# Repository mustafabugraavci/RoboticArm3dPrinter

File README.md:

# RoboticArm3dPrinter
Some kind of 3d printer

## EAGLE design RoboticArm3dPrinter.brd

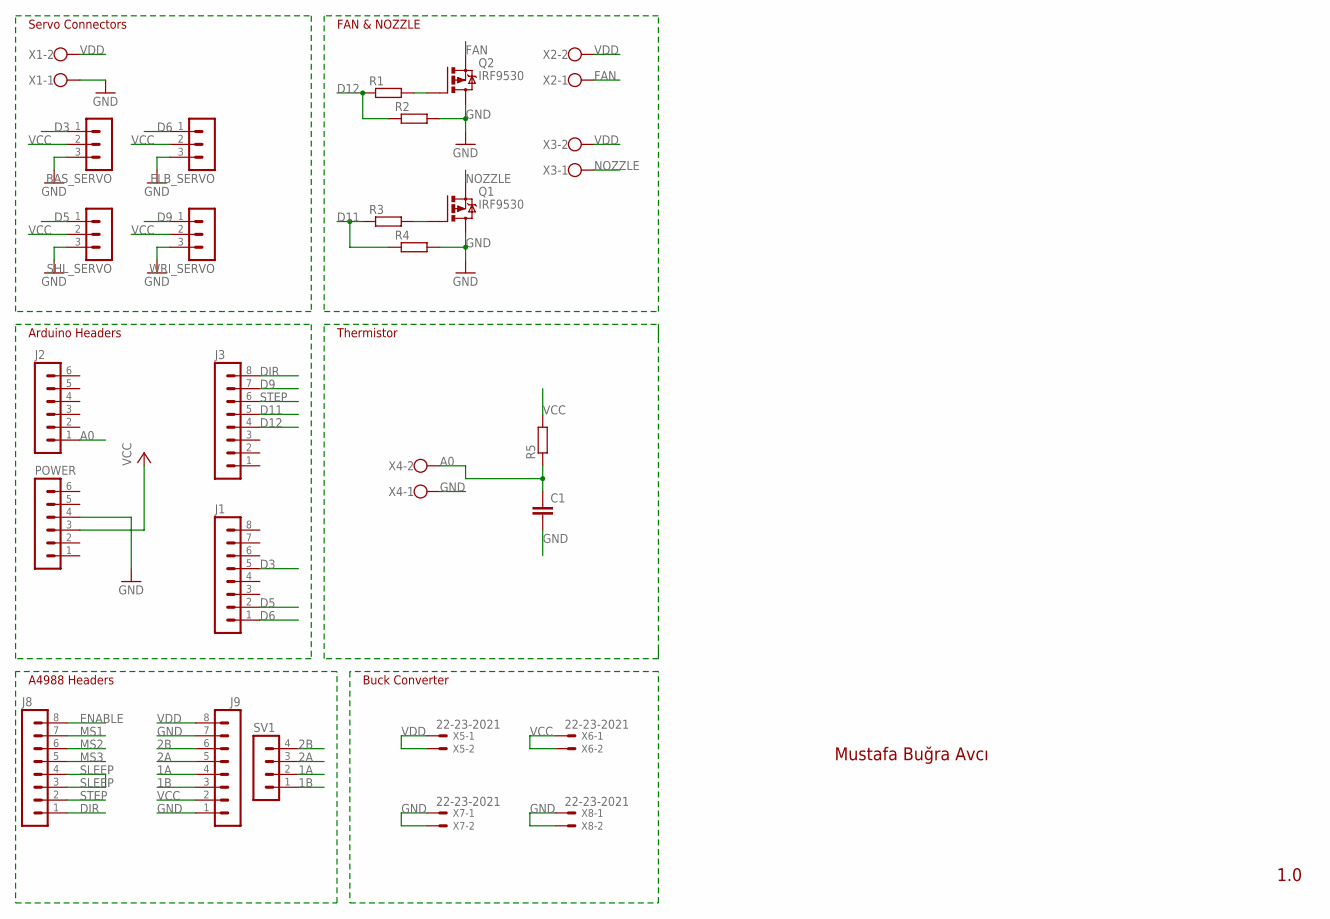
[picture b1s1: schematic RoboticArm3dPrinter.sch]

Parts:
BAS_SERVO: MA03-1
C1: C5/2.5; C5B2.5
ELB_SERVO: MA03-1
J1, J3, J8, J9: MA08-1
J2: MA06-1
POWER: MA06-1
Q1, Q2: IRF9530; TO220BV
R1, R2, R3, R4, R5: R-EU_0207/10; 0207/10
SHL_SERVO: MA03-1
SV1: MA04-1
WRI_SERVO: MA03-1
X1, X2, X3, X4: W237-102
X5, X6, X7, X8: 22-23-2021

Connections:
1A: J9.4, SV1.2
1B: J9.3, SV1.1
2A: J9.5, SV1.3
2B: J9.6, SV1.4
A0: C1.1, J2.1, R5.1, X4.2
D3: BAS_SERVO.1, J1.5
D5: J1.2, SHL_SERVO.1
D6: ELB_SERVO.1, J1.1
D9: J3.7, WRI_SERVO.1
D11: J3.5, R3.1, R4.1
D12: J3.4, R1.1, R2.1
DIR: J3.8, J8.1
ENABLE: J8.8
FAN: Q2.S, X2.1
GND: BAS_SERVO.3, C1.2, ELB_SERVO.3, J9.1, J9.7, POWER.4, Q1.D, Q2.D, R2.2, R4.2, SHL_SERVO.3, WRI_SERVO.3, X1.1, X4.1, X7.1, X7.2, X8.1, X8.2
MS1: J8.7
MS2: J8.6
MS3: J8.5
unnamed: Q1.G, R3.2
unnamed: Q2.G, R1.2
NOZZLE: Q1.S, X3.1
SLEEP: J8.3, J8.4
STEP: J3.6, J8.2
VCC: BAS_SERVO.2, ELB_SERVO.2, J9.2, POWER.3, R5.2, SHL_SERVO.2, WRI_SERVO.2, X6.1, X6.2
VDD: J9.8, X1.2, X2.2, X3.2, X5.1, X5.2

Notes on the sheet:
Servo Connectors
Arduino Headers
Mustafa Buğra Avcı
1.0
A4988 Headers
FAN & NOZZLE
Thermistor
Buck Converter

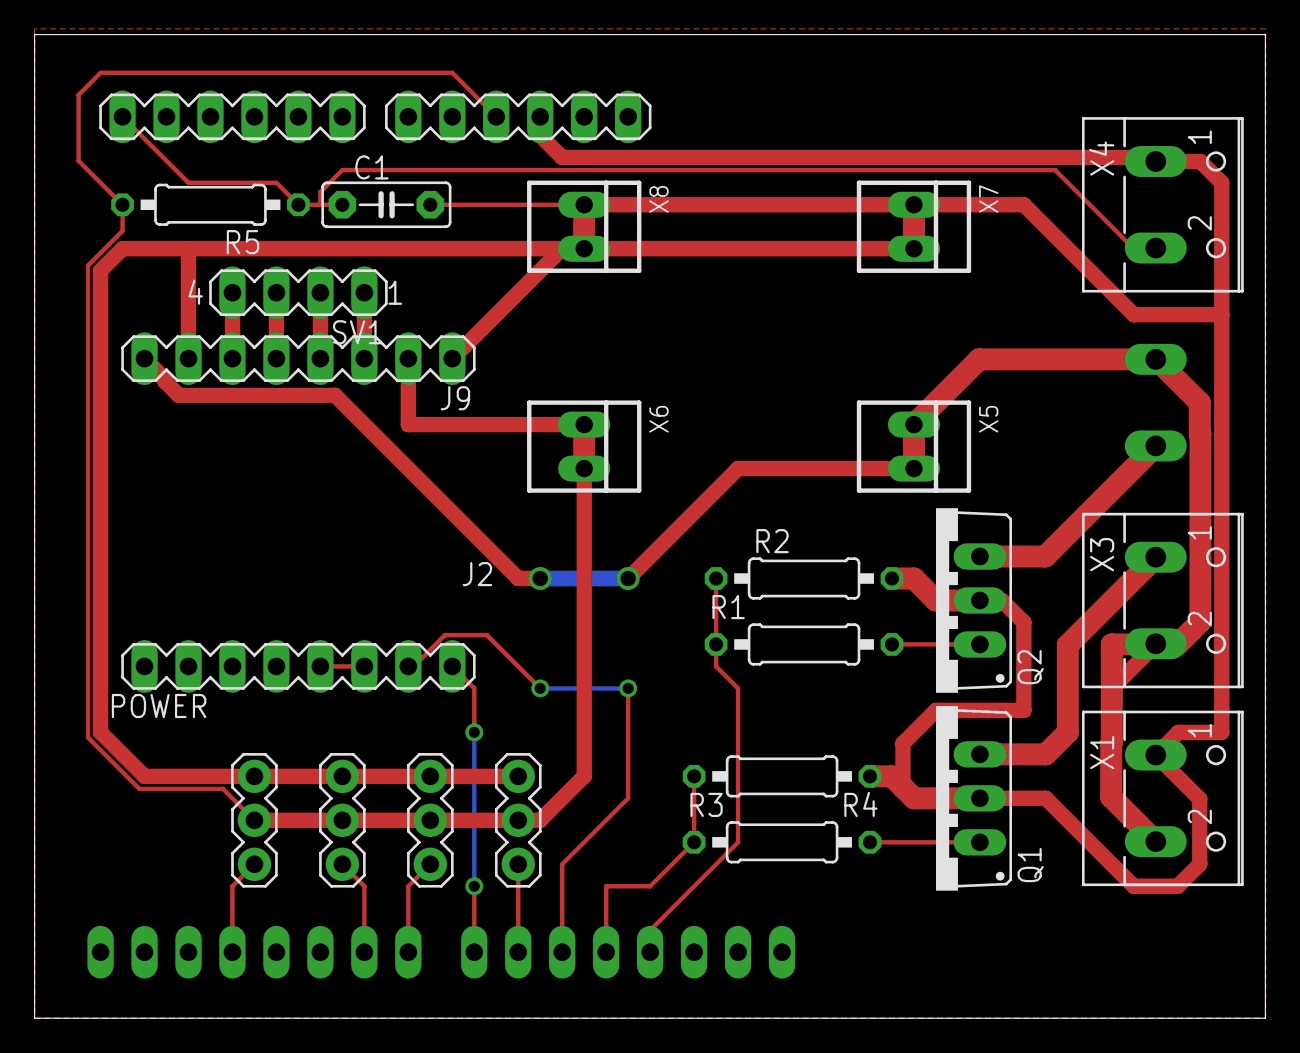
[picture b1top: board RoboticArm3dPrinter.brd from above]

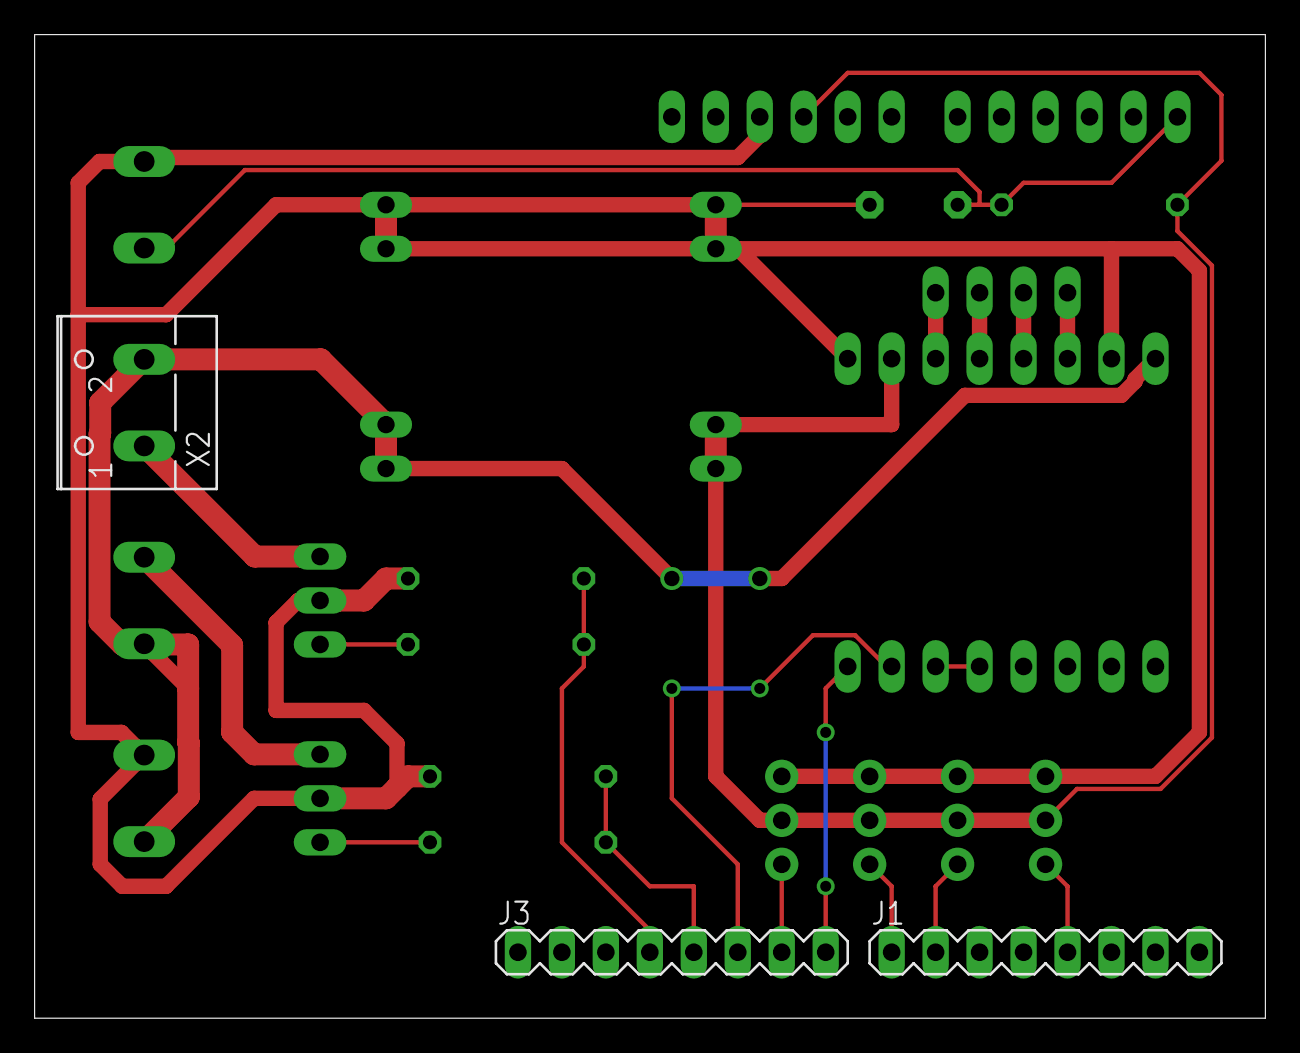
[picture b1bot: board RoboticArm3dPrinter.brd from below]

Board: 2 copper layers, 71.1 x 56.8 mm, 27 parts (3 on the bottom side), 21 nets.

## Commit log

2020-01-19 Create RoboticArm3dPrinter.ino
    //I will add nozzle, extruder and thermistor.
2020-01-19 Add files via upload
    Eagle Schematic
